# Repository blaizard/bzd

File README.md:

# bzd Framework

Access the [rendered version of this documentation](https://blaizard.github.io/bzd).

Fullstack, lightweight and flexible framework for IoT applications.
This mono-repository enables the following technologies:

|             C++20              |           Rust (2024)           |            Python 3.13            |           Node (v23)            |              Vue               |              Bazel               |              KiCad               |
| :----------------------------: | :-----------------------------: | :-------------------------------: | :-----------------------------: | :----------------------------: | :------------------------------: | :------------------------------: |
|  |  |  |  |  |  |  |

## Overview

This framework is built to run on all sorts of embedded platforms, from bare-metal 8-bit microcontrollers to high-performance compute units.
It is made to remove any dependency on the STL, but to provide a similar set of components and utilities to develop applications in an
efficient and safe manner.

It features the following:

- No dynamic allocations. All storage is declared either at compile time or on the stack.
- The core library is self-contained, with no reliance on third-party libraries, only on the freestanding C++ standard library.
- Flexible error handling model.
- Based on C++ coroutines.
- Compile-time string formatting tool.
- Lightweight.
- Useful set of containers.

## Platforms

The following target platforms are currently supported:

| Name                   | Compiler | Version | Executors   | Debug |
| ---------------------- | -------- | ------- | ----------- | ----- |
| linux_x86_64_clang\*   | clang    | 19.1.7  | host\*      |       |
| linux_x86_64_gcc       | gcc      | 14.2.0  | host\*      |       |
| esp32_xtensa_lx6_gcc   | gcc      | 14.2.0  | sim\*, uart | x     |
| esp32s3_xtensa_lx7_gcc | gcc      | 14.2.0  | sim\*, uart | x     |

\* Default.

When debug is supported by the platform, one can run a target with the `--config=debug` option and a debug environment will
be made available.

## Build

### Locally

To build everything, just run:

```bash
./tools/bazel test //...
```

This will build locally; it will fetch all tools needed to build on your machine.

### Remote

To build Bazel targets, simply run `./tools/bazel` with `--config=remote` appended.

For debugging purposes, toolchains can be run locally in a docker sandbox which is very similar to what runs on remote execution.
To enable this configuration, run `./tools/bazel` with `--config=docker`.

## Documentation

To build the full project documentation, run:

```bash
./tools/bazel run //docs
```

## Code Quality

All supported languages come with their own set of code quality related tools.
To run all static sanity checks, code formatters and documentation generators at once, run the following command:

```bash
./tools/bazel run //:sanitizer
```

To run all tests, run the following command:

```bash
./quality_gate
```

This is a non-exhaustive list of languages and their supported tools. In addition to that,
formatters and linters for YAML, JSON and Markdown are also available.

| Language | Formatters   | Code Analyzers                      | Code Coverage | Test Framework | Documentation |
| -------- | ------------ | ----------------------------------- | ------------- | -------------- | ------------- |
| C++      | clang-format | clang-tidy, asan, lsan, tsan, ubsan | Yes           | Yes            | doxygen-based |
| Python   | ruff         | ruff, mypy                          | Yes           | Yes            |               |
| Node     | prettier     | eslint                              | Yes           | Yes            |               |
| Skylark  | buildifier   | buildifier                          |               |                | stardoc       |

Update `compile_commands.json`

```bash
./tools/bazel run @bzd_sanitizer//aspects/compile_commands:build
```

Update `rust-project.json`

```bash
./tools/bazel run @rules_rust//tools/rust_analyzer:gen_rust_project -- //rust/...
```

## Naming Convention

The code in this repository follows several principles regarding naming conventions. The following rules are applied across languages.

- Files and directories are named lower case `snake_case` using only the characters matching the regex: `[a-z0-9_/.]`. This is enforced by tools/bazel_build/modules/bzd_sanitizer/actions/structure.
- Variables, constants, functions, concepts, namespaces are named in `camelCase`.
- All types are named in `PascalCase`.
- Non-public members (variables, functions...) are appended with a `_` character.
- All names avoid abbreviations.

## Memory Footprint

All classes offered by this library share the same objective: a fixed memory size. Their footprint or maximum size
is determined at compile time, ensuring no memory allocation at runtime, making this library ideal for any safety-critical application.

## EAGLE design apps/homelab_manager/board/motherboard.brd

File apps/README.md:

# Applications

This repository contains public and private applications.

## Private

A private application is using git submodules pointing to a private subrepository.
This allow public users to share and use the repository without accessing private applications.

Private applications can be added as follow. Assuming we create a new application called `dummy`.

```bash
git submodule add -b main https://git.myprivaterepo.com/dummy.git apps/dummy
```

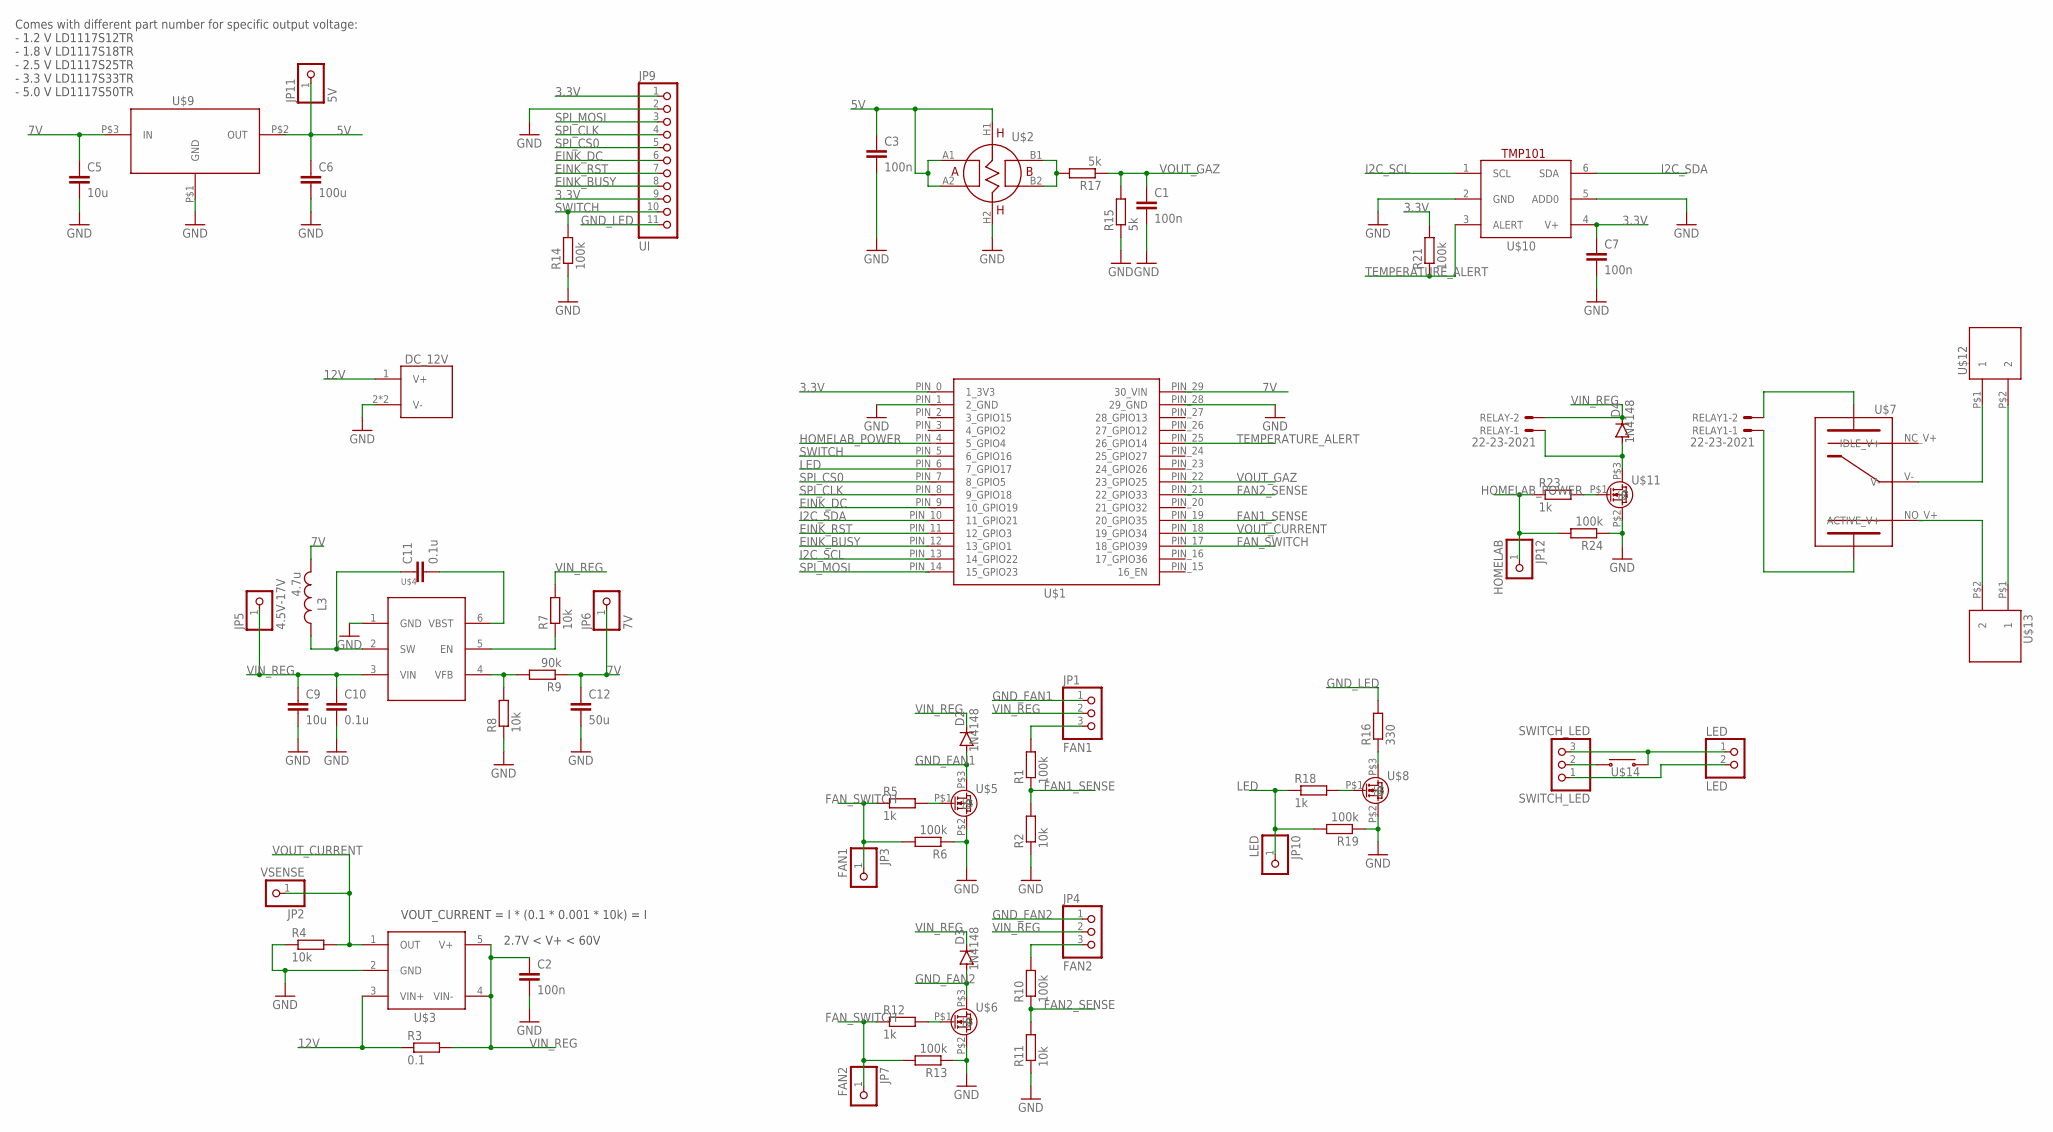
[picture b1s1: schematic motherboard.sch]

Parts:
C1, C2, C3, C7: 100n; C0805
C5, C9: 10u; C0805
C6: 100u; C0805
C10, C11: 0.1u; C0805
C12: 50u; C0805
D2, D3, D4: 1N4148; DO-214AC
DC_12V: DC_POWER_2.1MM
JP1: FAN1; 1X03
JP2: VSENSE; 1X01
JP3: FAN1; 1X01
JP4: FAN2; 1X03
JP5: 4.5V-17V; 1X01
JP6: 7V; 1X01
JP7: FAN2; 1X01
JP9: UI; 1X11
JP10: LED; 1X01
JP11: 5V; 1X01
JP12: HOMELAB; 1X01
L3: 4.7u; L3225M
LED: LED; 1X02
R1, R6, R10, R13, R14, R19, R21, R24: 100k; R0805
R2, R4, R7, R8, R11: 10k; R0805
R3: 0.1; R1206
R5, R12, R18, R23: 1k; R0805
R9: 90k; R0805
R15, R17: 5k; R0805
R16: 330; R0805
RELAY, RELAY1: 22-23-2021
SWITCH_LED: SWITCH_LED; 1X03
U$1: ESP32_DEVKIT_V1
U$2: MQ_2
U$3: INA169; SOT23_5_PIN
U$4: TPS561201; SOT23_6_PIN
U$5, U$6, U$8, U$11: MGSF1N03L; SOT23_3_PIN
U$7: RELAY_SONGLE
U$9: LD1117; SOT223_3_PIN
U$10: TMP101; SOT23_6_PIN
U$12, U$13: SCREW_TERMINAL
U$14: MOMENTARY_SWITCH

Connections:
3.3V: C7.1, JP9.1, JP9.9, R21.2, U$1.PIN_0 (1_3V3), U$10.4 (V+)
5V: C3.1, C6.1, JP11.1, U$2.A1, U$2.A2, U$2.H1, U$9.P$2 (OUT)
7V: C5.1, C12.1, JP6.1, L3.2, R9.1, U$1.PIN_29 (30_VIN), U$9.P$3 (IN)
12V: DC_12V.1 (V+), R3.1, U$3.3 (VIN+)
EINK_BUSY: JP9.8, U$1.PIN_12 (13_GPIO1)
EINK_DC: JP9.6, U$1.PIN_9 (10_GPIO19)
EINK_RST: JP9.7, U$1.PIN_11 (12_GPIO3)
FAN1_SENSE: R1.1, R2.2, U$1.PIN_19 (20_GPIO35)
FAN2_SENSE: R10.1, R11.2, U$1.PIN_21 (22_GPIO33)
FAN_SWITCH: JP3.1, JP7.1, R5.1, R6.2, R12.1, R13.2, U$1.PIN_17 (18_GPIO39)
GND: C1.2, C2.2, C3.2, C5.2, C6.2, C7.2, C9.2, C10.2, C12.2, DC_12V.2 (V-), DC_12V.3 (V-), JP9.2, R2.1, R4.1, R6.1, R8.1, R11.1, R13.1, R14.1, R15.1, R19.1, R24.1, U$1.PIN_1 (2_GND), U$1.PIN_28 (29_GND), U$2.H2, U$3.2 (GND), U$4.1 (GND), U$5.P$2 (S), U$6.P$2 (S), U$8.P$2 (S), U$9.P$1 (GND), U$10.2 (GND), U$10.5 (ADD0), U$11.P$2 (S)
GND_FAN1: D2.A, JP1.1, U$5.P$3 (D)
GND_FAN2: D3.A, JP4.1, U$6.P$3 (D)
GND_LED: JP9.11, R16.2
GND_RELAY: D4.A, RELAY.1, U$11.P$3 (D)
HOMELAB_POWER: JP12.1, R23.1, R24.2, U$1.PIN_4 (5_GPIO4)
I2C_SCL: U$1.PIN_13 (14_GPIO22), U$10.1 (SCL)
I2C_SDA: U$1.PIN_10 (11_GPIO21), U$10.6 (SDA)
LED: JP10.1, R18.1, R19.2, U$1.PIN_6 (7_GPIO17)
unnamed: JP1.3, R1.2
unnamed: R5.2, U$5.P$1 (G)
unnamed: JP4.3, R10.2
unnamed: R12.2, U$6.P$1 (G)
unnamed: R17.2, U$2.B1, U$2.B2
unnamed: RELAY1.2, U$7.COMMAND_V+
unnamed: LED.1, SWITCH_LED.3, U$14.B1, U$14.B2
unnamed: R18.2, U$8.P$1 (G)
unnamed: C11.2, U$4.6 (VBST)
unnamed: R7.1, U$4.5 (EN)
unnamed: R8.2, R9.2, U$4.4 (VFB)
unnamed: C11.1, L3.1, U$4.2 (SW)
unnamed: R23.2, U$11.P$1 (G)
unnamed: R16.1, U$8.P$3 (D)
unnamed: RELAY1.1, U$7.COMMAND_V-
unnamed: U$12.P$2 (2), U$13.P$1 (1)
unnamed: U$7.V-, U$12.P$1 (1)
unnamed: U$7.NO_V+ (ACTIVE_V+), U$13.P$2 (2)
unnamed: LED.2, SWITCH_LED.1
unnamed: SWITCH_LED.2, U$14.A1, U$14.A2
SPI_CLK: JP9.4, U$1.PIN_8 (9_GPIO18)
SPI_CS0: JP9.5, U$1.PIN_7 (8_GPIO5)
SPI_MOSI: JP9.3, U$1.PIN_14 (15_GPIO23)
SWITCH: JP9.10, R14.2, U$1.PIN_5 (6_GPIO16)
TEMPERATURE_ALERT: R21.1, U$1.PIN_25 (26_GPIO14), U$10.3 (ALERT)
VIN_REG: C2.1, C9.1, C10.1, D2.C, D3.C, D4.C, JP1.2, JP4.2, JP5.1, R3.2, R7.2, RELAY.2, U$3.4 (VIN-), U$3.5 (V+), U$4.3 (VIN)
VOUT_CURRENT: JP2.1, R4.2, U$1.PIN_18 (19_GPIO34), U$3.1 (OUT)
VOUT_GAZ: C1.1, R15.2, R17.1, U$1.PIN_22 (23_GPIO25)

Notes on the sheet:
2.7V < V+ < 60V
VOUT_CURRENT = I * (0.1 * 0.001 * 10k) = I
Comes with different part number for specific output voltage: - 1.2 V LD1117S12TR - 1.8 V LD1117S18TR - 2.5 V LD1117S25TR - 3.3 V LD1117S33TR - 5.0 V LD1117S50TR

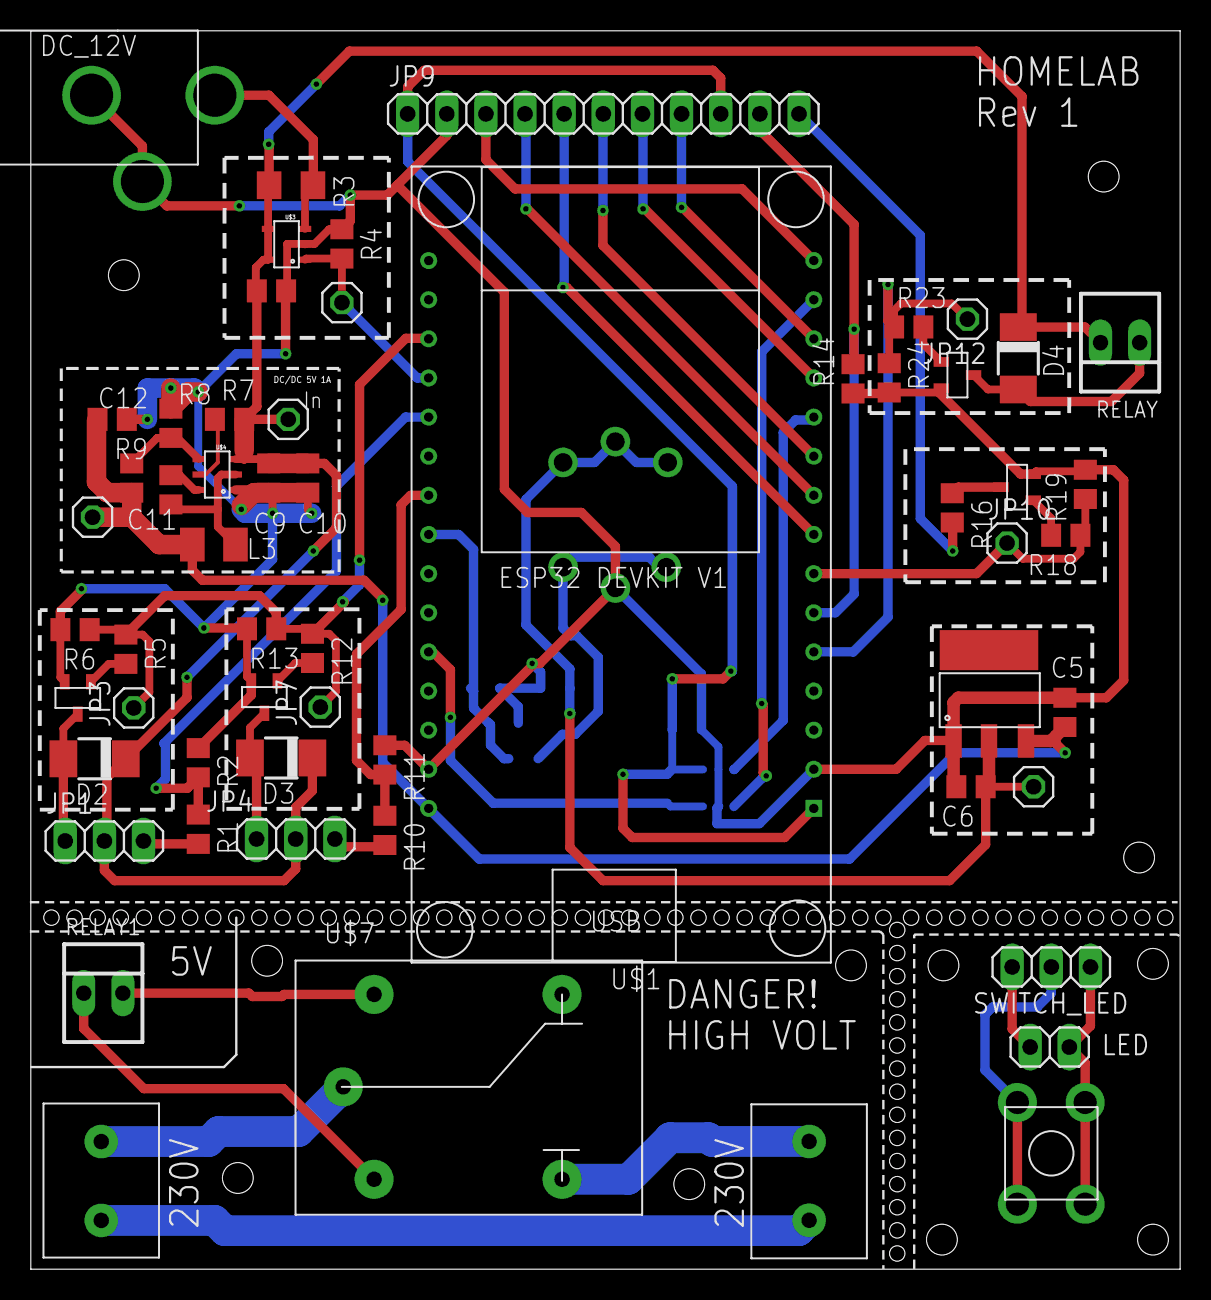
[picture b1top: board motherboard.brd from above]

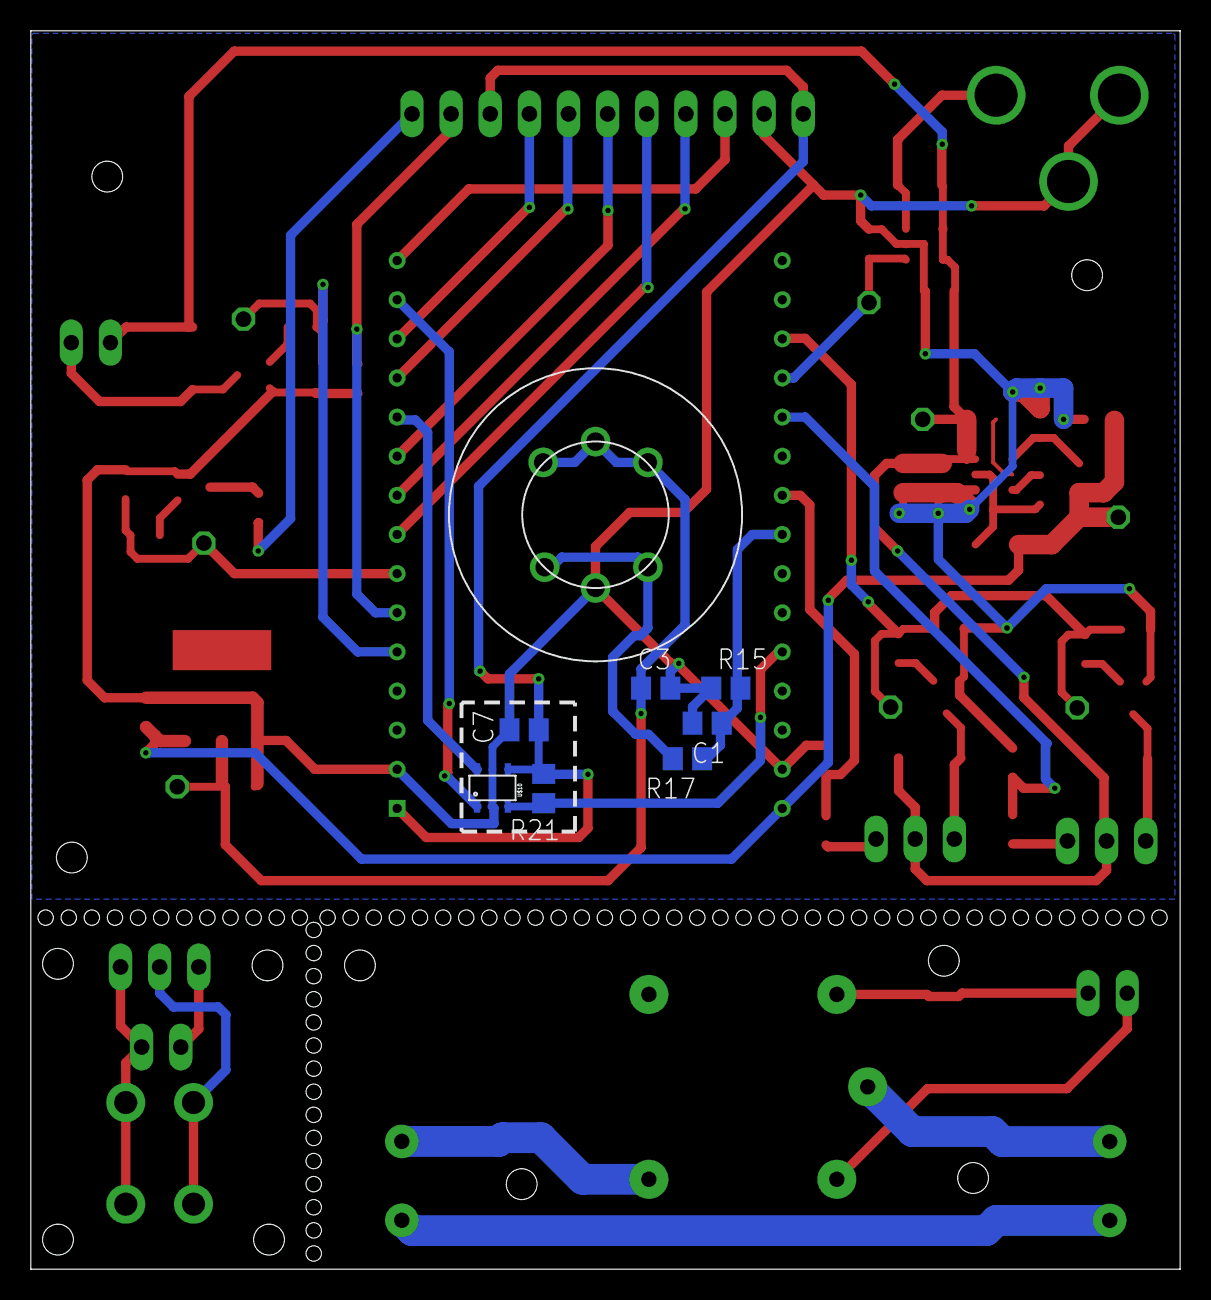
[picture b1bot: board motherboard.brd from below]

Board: 2 copper layers, 74.6 x 80.4 mm, 66 parts (8 on the bottom side), 47 nets.

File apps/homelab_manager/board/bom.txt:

Partlist exported from /home/dummy1/projects/cpp-coroutines/apps/homelab_manager/board/motherboard.sch at 03.10.20 10:38

Qty Value            Device           Package          Parts                                Description                          MF    MPN        OC_FARNELL OC_NEWARK POPULARITY SPICEPREFIX
1   0.1              R-EU_R1206       R1206            R3                                   RESISTOR, European symbol                                                  41         R          
2   0.1u             C-EUC0805        C0805            C10, C11                             CAPACITOR, European symbol                                                 88         C          
8   100k             R-EU_R0805       R0805            R1, R6, R10, R13, R14, R19, R21, R24 RESISTOR, European symbol                                                  86         R          
4   100n             C-EUC0805        C0805            C1, C2, C3, C7                       CAPACITOR, European symbol                                                 88         C          
1   100u             C-EUC0805        C0805            C6                                   CAPACITOR, European symbol                                                 88         C          
5   10k              R-EU_R0805       R0805            R2, R4, R7, R8, R11                  RESISTOR, European symbol                                                  86         R          
2   10u              C-EUC0805        C0805            C5, C9                               CAPACITOR, European symbol                                                 88         C          
3   1N4148           DIODE-DO-214AC   DO-214AC         D2, D3, D4                           DIODE                                                                      25                    
4   1k               R-EU_R0805       R0805            R5, R12, R18, R23                    RESISTOR, European symbol                                                  86         R          
2   22-23-2021       22-23-2021       22-23-2021       RELAY, RELAY1                        .100" (2.54mm) Center Header - 2 Pin MOLEX 22-23-2021 1462926    25C3832   40                    
1   330              R-EU_R0805       R0805            R16                                  RESISTOR, European symbol                                                  86         R          
1   4.5V-17V         PINHD-1X1        1X01             JP5                                  PIN HEADER                                                                 64                    
1   4.7u             L-USL3225M       L3225M           L3                                   INDUCTOR, American symbol                                                  11         L          
1   50u              C-EUC0805        C0805            C12                                  CAPACITOR, European symbol                                                 88         C          
1   5V               PINHD-1X1        1X01             JP11                                 PIN HEADER                                                                 64                    
2   5k               R-EU_R0805       R0805            R15, R17                             RESISTOR, European symbol                                                  86         R          
1   7V               PINHD-1X1        1X01             JP6                                  PIN HEADER                                                                 64                    
1   90k              R-EU_R0805       R0805            R9                                   RESISTOR, European symbol                                                  86         R          
1   DC_POWER_2.1MM   DC_POWER_2.1MM   DC_POWER_2.1MM   DC_12V                                                                                                                                
1   ESP32_DEVKIT_V1  ESP32_DEVKIT_V1  ESP32_DEVKIT_V1  U$1                                                                                                                                   
1   FAN1             PINHD-1X1        1X01             JP3                                  PIN HEADER                                                                 64                    
1   FAN1             PINHD-1X3        1X03             JP1                                  PIN HEADER                                                                 92                    
1   FAN2             PINHD-1X1        1X01             JP7                                  PIN HEADER                                                                 64                    
1   FAN2             PINHD-1X3        1X03             JP4                                  PIN HEADER                                                                 92                    
1   HOMELAB          PINHD-1X1        1X01             JP12                                 PIN HEADER                                                                 64                    
1   INA169           INA169           SOT23_5_PIN      U$3                                                                                                                                   
1   LD1117           LD1117           SOT223_3_PIN     U$9                                                                                                                                   
1   LED              PINHD-1X1        1X01             JP10                                 PIN HEADER                                                                 64                    
1   LED              PINHD-1X2        1X02             LED                                  PIN HEADER                                                                 98                    
4   MGSF1N03L        MGSF1N03L        SOT23_3_PIN      U$5, U$6, U$8, U$11                                                                                                                   
1   MOMENTARY_SWITCH MOMENTARY_SWITCH MOMENTARY_SWITCH U$14                                                                                                                                  
1   MQ_2             MQ_2             MQ_2             U$2                                                                                                                                   
1   RELAY_SONGLE     RELAY_SONGLE     RELAY_SONGLE     U$7                                                                                                                                   
2   SCREW_TERMINAL   SCREW_TERMINAL   SCREW_TERMINAL   U$12, U$13                                                                                                                            
1   SWITCH_LED       PINHD-1X3        1X03             SWITCH_LED                           PIN HEADER                                                                 92                    
1   TMP101           TMP101           SOT23_6_PIN      U$10                                                                                                                                  
1   TPS561201        TPS561201        SOT23_6_PIN      U$4                                                                                                                                   
1   UI               PINHD-1X11       1X11             JP9                                  PIN HEADER                                                                 12                    
1   VSENSE           PINHD-1X1        1X01             JP2                                  PIN HEADER                                                                 64
